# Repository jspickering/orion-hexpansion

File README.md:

# Orion Starspansion

This is an Orion starspansion (hexpansion) for the [EMF Tildagon badge](https://github.com/emfcamp/badge-2024-hardware)

There's a [CAD model](/badge_model/Starspansion.f3z) if you want to see the complete hexpansion.

The guide below shows you which parts you need to make one yourself, and how to assemble it.

## Materials

### Core
These are all the materials you will need to create the hexpansion. We've linked to the exact products we used, but you can get them from whichever retailer you prefer.

* Transparent acrylic sheet (1-3mm thick) ([Hobarts](https://hobarts.com/products/clear-cast-perspex-acrylic?variant=43939414245613))
* Opaque acrylic sheet (1-3mm thick) ([Hobarts](https://hobarts.com/collections/galaxy-acrylic))
* Custom starspansion PCB ([JLCPCB](https://jlcpcb.com/), see [appendix](#appendix) for details on how to order them)
* 2mm LEDs ([Switch Electronics](https://www.switchelectronics.co.uk/products/cool-white-2mm-lighthouse-diffused-lens-led-750mcd))
* 2x 20R resistors ([PiHut](https://thepihut.com/products/resistor-packs?variant=37986550513859))
* 5x 100R resistors ([PiHut](https://thepihut.com/products/resistor-packs?variant=37986550579395))
* 4x 1,000R resistors ([PiHut](https://thepihut.com/products/resistor-packs?variant=37986550710467))
* 3D printing filament ([Filamentive](https://www.filamentive.com/product/light-wood-3d-printing-filament-1-75mm-500g/))
* 4x threaded brass inserts (M2 x 2 x 3.2) ([Amazon](https://www.amazon.co.uk/gp/aw/d/B0D41PW4GC?psc=1&ref=ppx_pop_mob_b_asin_title))
* 4x screws (M2 x 4) ([Amazon](https://www.amazon.co.uk/Premium-410-Piece-M2-Socket-Screw/dp/B0C1BMQK6T/ref=sr_1_10?dib=eyJ2IjoiMSJ9.ec2XkPjCTLphyCur4SjV1LYcDcoA4TuZfBRzJcCsZN54BXxc_tUUpMuCt5Guri9d9htPosCR-P9NZW7xD_XmA6NsZV3yxVAkDmSuLtaEWaK1z3YoWK5AJ6ooLgJkEJZBYKWCMzO-kyaV45lJbb8jfivTh59yqgS2k-A5ZM3MbI0ZODj77Q6jHUXQh-KLEhTx87yF_xTg8F0XrKIwPlFFHzyhw1RVGwhEqmd6leQLgxVd2MB7YCY5vhOgiUnW6GbrY0Hhkpiv1ALGMNfxzY1rKijh1VJ5ixGamhHxsz14tdk.U6UQpYHKPmatvGg9KSllMK7prQMRhpIz6KX31xTBUUw&dib_tag=se&keywords=m2%2Bscrews&qid=1784233113&sr=8-10&th=1))

### Optional
This is not necessary, but we used it when we created our version of the hexpansion.
* Wood stain (if using wood-based printing material)
* 2x M2 size screws to attach the hexpansion more securely to the badge

## Tools and equipment

* soldering iron + solder
* 3D printer
* laser cutter

## Processes

1) 3D print the three separate components of the chassis, using the design files for the [outer section](/printing_files/outer_section.stl), [middle](/printing_files/middle.stl), and [base](/printing_files/base.stl). We used a wood-based filament which we then sanded down and applied 3 coats of wood stain to. But you can use any filament you want.

2)  Using a laser cutter, cut the acrylic sheets. The top one should be cut with the design file for the [top layer without holes](/laser_cutting_files/acrylic_no_holes.dxf), and the bottom one with the design file for the [second layer with holes](/laser_cutting_files/acrylic_holes.dxf).

We used a transparent acrylic sheet for the top (1mm thick) just to add a bit of protection, and a galaxy-style sheet for the second layer (3mm thick) for a more space-themed look. You can play around with different kinds, such as a translucent top sheet for a more diffused look. As long as the two layers total 4mm thick, everything else should slot together without needing to change any other aspects of the design.

3) Solder the LEDs and resistors into the custom PCB. Here's how the LEDs and resistors map on (see the PCB itself), to get the correct magnitude for each star:

| LED ref | Resistor ref | Resistor value |
| ------------- | ------------- | ------------- |
| D1 | R1 | 20R |
| D2 | R2 | 20R |
| D3 | R3 | 100R |
| D4 | R4 | 100R |
| D5 | R5 | 100R |
| D6 | R6 | 100R |
| D7 | R7 | 100R |
| D8 | R8 | 1,000R |
| D9 | R9 | 1,000R |
| D10 | R10 | 1,000R |
| D11 | R11| 1,000R |

When you first put the LEDs in, you should use the middle part of the 3D printed chassis to ensure they're in the correct position before soldering (each pointed part of the LED should be visible in the holes when looking at it top-down -- there are some screw holes to help you hold it together if needed. You may need to take it off and put it back on a few times as you go. Finish with it slotted into the PCB and LEDs.

4) Take the base chassis piece, and gently place one of the brass inserts into one of the four holes (from the outside in). Using the soldering iron, gently place the tip on the insert and, using the heat of the iron, VERY SLOWLY AND CAREFULLY apply pressure so that the insert moves in. Ensure that it sits flush with the chassis piece. Repeat for the other 3 holes.

5) You can now start assembling the hexpansion. Take the outer section chassis piece, and slot the top layer acrylic in, followed by the second layer acrylic, followed by the PCB and middle chassis piece (middle chassis piece on top), and then the base chassis piece.

Take the four screws and secure the base piece to the middle piece (outside in), using the inserts to thread in the screws. Don't screw it too tightly.

And there it is. A complete Orion Starspansion hexpansion!

# Appendix
## Ordering the PCB
If you'd like to customise the PCB we've provided a [KiCad project](/PCB/starspansion_kicad/). If you just want to order the PCB, all you need is the [gerbers](/PCB/starspansion_kicad/gerbers.zip) .zip file. Head over to JLCPCB.com (or a PCB manufacturer of your choice) and select 'Order Now'. Drag and drop the gerbers .zip (or select 'Add gerber file') onto the upload area amd wait a few moments until the upload is complete and a visual representation of the PCB is displayed. The existing settings will be correct for the most part with two important exceptions:

* PCB Thickness: 1mm
* Surface Finish: ENIG

Feel free to choose the colour and number or copies as you'd like. Once you've chosen the settings, choose 'SAVE TO CART' and you can go ahead and head to your basket and place the order.

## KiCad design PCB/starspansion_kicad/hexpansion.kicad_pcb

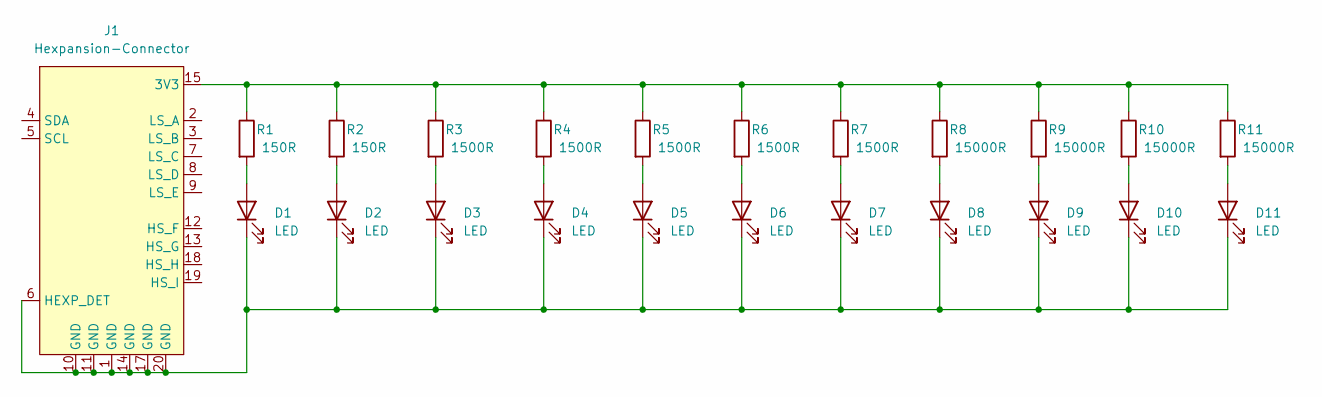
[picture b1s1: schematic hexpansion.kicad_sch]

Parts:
D1, D2, D3, D4, D5, D6, D7, D8, D9, D10, D11: LED; LED_D1.8mm_W3.3mm_H2.4mm
J1: Hexpansion-Connector; hexpansion-edge-connector
R1, R2: 150R; R_Axial_DIN0207_L6.3mm_D2.5mm_P10.16mm_Horizontal
R3, R4, R5, R6, R7: 1500R; R_Axial_DIN0207_L6.3mm_D2.5mm_P10.16mm_Horizontal
R8, R9, R10, R11: 15000R; R_Axial_DIN0207_L6.3mm_D2.5mm_P10.16mm_Horizontal

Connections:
unnamed: D1.2 (A), R1.2
unnamed: D1.1 (K), D2.1 (K), D3.1 (K), D4.1 (K), D5.1 (K), D6.1 (K), D7.1 (K), D8.1 (K), D9.1 (K), D10.1 (K), D11.1 (K), J1.1 (GND), J1.6 (HEXP_DET), J1.10 (GND), J1.11 (GND), J1.14 (GND), J1.17 (GND), J1.20 (GND)
unnamed: D2.2 (A), R2.2
unnamed: D3.2 (A), R3.2
unnamed: D4.2 (A), R4.2
unnamed: D5.2 (A), R5.2
unnamed: D6.2 (A), R6.2
unnamed: D7.2 (A), R7.2
unnamed: D8.2 (A), R8.2
unnamed: D9.2 (A), R9.2
unnamed: D10.2 (A), R10.2
unnamed: D11.2 (A), R11.2
unnamed: J1.15 (3V3), J1.16 (3V3), R1.1, R2.1, R3.1, R4.1, R5.1, R6.1, R7.1, R8.1, R9.1, R10.1, R11.1

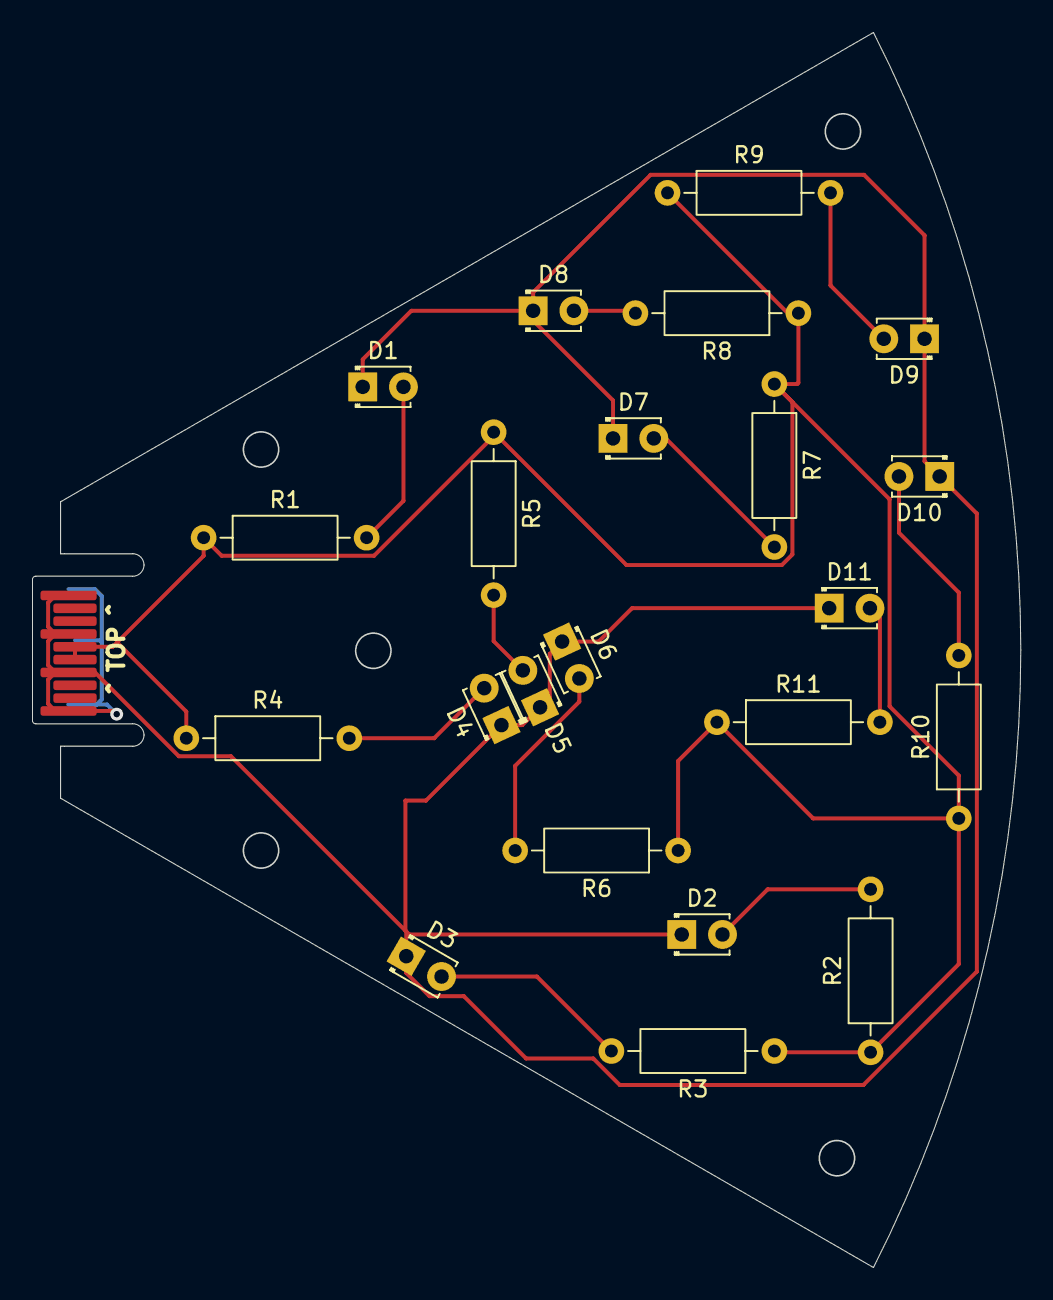
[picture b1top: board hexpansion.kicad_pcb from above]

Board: 2 copper layers, 61.6 x 77.0 mm, 23 parts (0 on the bottom side), 13 nets.
